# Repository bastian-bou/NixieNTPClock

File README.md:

# NixieNTPClock
Nixie clock around ESP32 connected to a NTP server

You can find the KiCad project and gerbers in **Hardware** folder and the PlatformIO project with arduino framwork in **Software** project

I am using ESP32 WROOM 32

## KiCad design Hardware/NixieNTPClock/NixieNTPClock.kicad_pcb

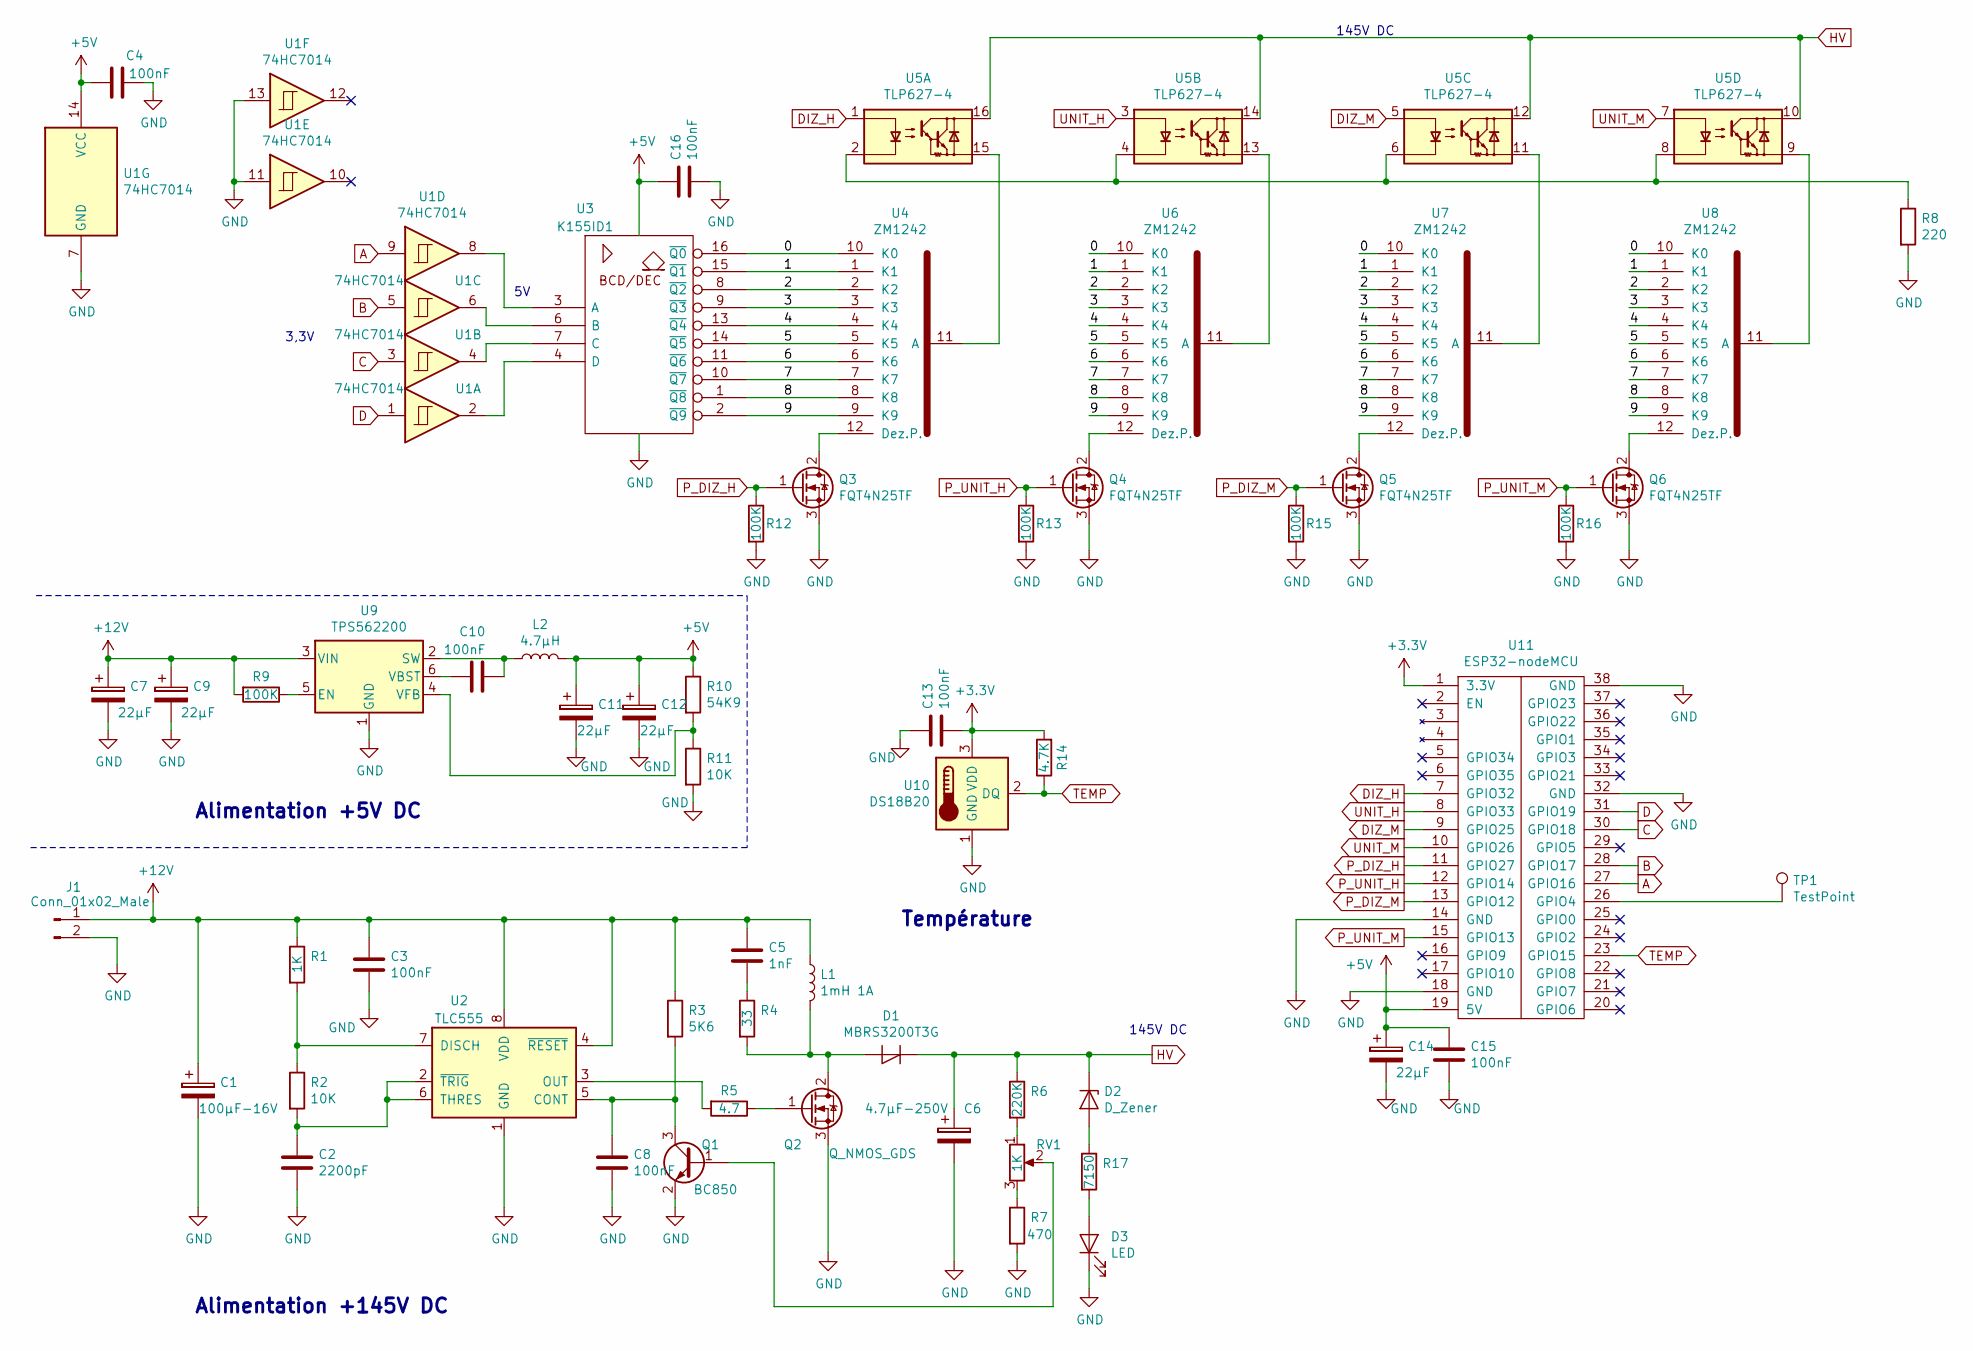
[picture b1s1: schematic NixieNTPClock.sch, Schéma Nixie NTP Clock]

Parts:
C1: 100µF-16V; CP_Elec_6.3x7.7; Farnell 1850114
C2: 2200pF; C_0603_HandSoldering; Farnell 2470451
C3, C4, C8, C10, C13, C15, C16: 100nF; C_0805_HandSoldering; Farnell 1740665
C5: 1nF; C_0603_HandSoldering
C6: 4.7µF-250V; CP_Elec_10x7.7; Farnell 2326350
C7, C9, C11, C12, C14: 22µF; CP_Elec_5x5.8; Farnell 9695737
D1: MBRS3200T3G; D_SMB_Handsoldering; Farnell 1838812
D2: D_Zener; D_SMB_Handsoldering; Farnell 2844801
D3: LED; D_0603; Farnell 8529833
J1: Conn_01x02_Male; PINHEAD1-2
L1: 1mH 1A; Inductor_Wurth_HCI-1335; Farnell 2288316
L2: 4.7µH; SELF-WE-TPC_M; Farnell 2066938
Q1: BC850; SOT-23W_Handsoldering; Farnell 1081241
Q2: Q_NMOS_GDS; TO-252-2; Farnell 2453852
Q3, Q4, Q5, Q6: FQT4N25TF; SOT-223-3_TabPin2; Farnell 2453914
R1: 1K; R_1206_HandSoldering
R2, R11: 10K; R_1206_HandSoldering
R3: 5K6; R_1206_HandSoldering
R4: 33; R_1206_HandSoldering
R5: 4.7; R_1206_HandSoldering
R6: 220K; R_1206_HandSoldering
R7: 470; R_1206_HandSoldering
R8: 220; R_1206_HandSoldering
R9, R12, R13, R15, R16: 100K; R_1206_HandSoldering
R10: 54K9; R_1206_HandSoldering
R14: 4.7K; R_1206_HandSoldering
R17: 7150; R_1206_HandSoldering; Farnell 2307836
RV1: 1K; Potentiometer_Trimmer_Vishay_TS53YJ; Farnell 1141482
TP1: TestPoint; touch
U1: 74HC7014; SOIC-14_3.9x8.7mm_Pitch1.27mm; Farnell 2777749
U2: TLC555; DIP-8_W7.62mm_SMDSocket_SmallPads
U3: K155ID1; DIP-16_W7.62mm_Socket
U4, U6, U7, U8: ZM1242
U5: TLP627-4; DIP-16_W7.62mm_Socket_LongPads; Farnell 1225840
U9: TPS562200; SOT-23-6; Farnell 2781737
U10: DS18B20; TO-92_Inline_Wide
U11: ESP32-nodeMCU; ESP32 NodeMCU AZ

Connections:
+3V3: C13.2, R14.2, U10.3 (VDD), U11.1 (3.3V)
+5V: C4.1, C11.1, C12.1, C14.1, C15.1, C16.1, L2.2, R10.1, U1.14 (VCC), U3.5 (VCC), U11.19 (5V)
+12V: C1.1, C3.1, C5.1, C7.1, C9.1, J1.1, L1.1, R1.1, R3.1, R9.2, U2.4 (~RESET), U2.8 (VDD), U9.3 (VIN)
/0: U3.16 (~Q0), U4.10 (K0), U6.10 (K0), U7.10 (K0), U8.10 (K0)
/1: U3.15 (~Q1), U4.1 (K1), U6.1 (K1), U7.1 (K1), U8.1 (K1)
/2: U3.8 (~Q2), U4.2 (K2), U6.2 (K2), U7.2 (K2), U8.2 (K2)
/3: U3.9 (~Q3), U4.3 (K3), U6.3 (K3), U7.3 (K3), U8.3 (K3)
/4: U3.13 (~Q4), U4.4 (K4), U6.4 (K4), U7.4 (K4), U8.4 (K4)
/5: U3.14 (~Q5), U4.5 (K5), U6.5 (K5), U7.5 (K5), U8.5 (K5)
/6: U3.11 (~Q6), U4.6 (K6), U6.6 (K6), U7.6 (K6), U8.6 (K6)
/7: U3.10 (~Q7), U4.7 (K7), U6.7 (K7), U7.7 (K7), U8.7 (K7)
/8: U3.1 (~Q8), U4.8 (K8), U6.8 (K8), U7.8 (K8), U8.8 (K8)
/9: U3.2 (~Q9), U4.9 (K9), U6.9 (K9), U7.9 (K9), U8.9 (K9)
A: U1.9, U11.27 (GPIO16)
B: U1.5, U11.28 (GPIO17)
C: U1.3, U11.30 (GPIO18)
D: U1.1, U11.31 (GPIO19)
DIZ_H: U5.1, U11.7 (GPIO32)
DIZ_M: U5.5, U11.9 (GPIO25)
GND: C1.2, C2.2, C3.2, C4.2, C6.2, C7.2, C8.2, C9.2, C11.2, C12.2, C13.1, C14.2, C15.2, C16.2, D3.1 (K), J1.2, Q1.2 (E), Q2.3 (S), Q3.3 (S), Q4.3 (S), Q5.3 (S), Q6.3 (S), R7.2, R8.2, R11.2, R12.2, R13.2, R15.2, R16.2, U1.7 (GND), U1.11, U1.13, U2.1 (GND), U3.12 (GND), U9.1 (GND), U10.1 (GND), U11.14 (GND), U11.18 (GND), U11.32 (GND), U11.38 (GND)
HV: C6.1, D1.1 (K), D2.1 (K), R6.1, U5.10, U5.12, U5.14, U5.16
unnamed: C2.1, R2.2, U2.2 (~TRIG), U2.6 (THRES)
unnamed: C5.2, R4.1
unnamed: C8.1, Q1.3 (C), R3.2, U2.5 (CONT)
unnamed: C10.1, U9.6 (VBST)
unnamed: C10.2, L2.1, U9.2 (SW)
unnamed: D1.2 (A), L1.2, Q2.2 (D), R4.2
unnamed: D2.2 (A), R17.1
unnamed: D3.2 (A), R17.2
unnamed: Q1.1 (B), RV1.2
unnamed: Q2.1 (G), R5.1
unnamed: Q3.2 (D), U4.12 (Dez.P.)
unnamed: Q4.2 (D), U6.12 (Dez.P.)
unnamed: Q5.2 (D), U7.12 (Dez.P.)
unnamed: Q6.2 (D), U8.12 (Dez.P.)
unnamed: R1.2, R2.1, U2.7 (DISCH)
unnamed: R5.2, U2.3 (OUT)
unnamed: R6.2, RV1.1
unnamed: R7.1, RV1.3
unnamed: R8.1, U5.2, U5.4, U5.6, U5.8
unnamed: R9.1, U9.5 (EN)
unnamed: R10.2, R11.1, U9.4 (VFB)
unnamed: TP1.1, U11.26 (GPIO4)
unnamed: U1.2, U3.4 (D)
unnamed: U1.4, U3.7 (C)
unnamed: U1.6, U3.6 (B)
unnamed: U1.8, U3.3 (A)
unnamed: U4.11 (A), U5.15
unnamed: U5.9, U8.11 (A)
unnamed: U5.11, U7.11 (A)
unnamed: U5.13, U6.11 (A)
P_DIZ_H: Q3.1 (G), R12.1, U11.11 (GPIO27)
P_DIZ_M: Q5.1 (G), R15.1, U11.13 (GPIO12)
P_UNIT_H: Q4.1 (G), R13.1, U11.12 (GPIO14)
P_UNIT_M: Q6.1 (G), R16.1, U11.15 (GPIO13)
TEMP: R14.1, U10.2 (DQ), U11.23 (GPIO15)
UNIT_H: U5.3, U11.8 (GPIO33)
UNIT_M: U5.7, U11.10 (GPIO26)

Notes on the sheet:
145V DC
3,3V
Alimentation +5V DC
Alimentation +145V DC
Température

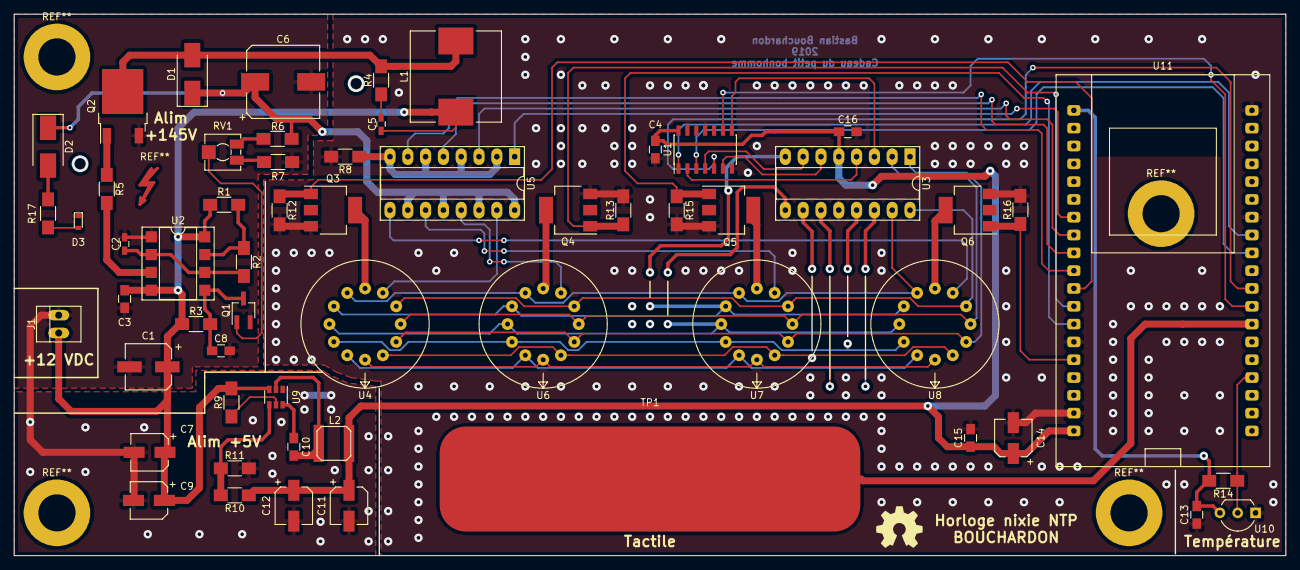
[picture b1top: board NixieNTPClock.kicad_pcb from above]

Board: 4 copper layers, 181.4 x 77.2 mm, 58 parts (0 on the bottom side), 58 nets.

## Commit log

2019-10-21 Update README.md
    Add comments on library and folders description
2019-10-22 add Hardware and Software folders
2019-10-27 Add kicad project files with a beginning of schematic (high voltage power supply unit)
2019-10-27 Add documentation with siemens datasheet Add farnel refs and component refs in schematic
2019-10-27 Add nixie command in schema, nixie library in project and pdf in documentation
2019-10-28 remove DOC folder
2019-10-28 nixie command finished, add 5V DC power supply and temp sensor
2019-10-28 Add command code for farnell in schematic
2019-10-29 Add ESP32 NODE MCU library + labels for connection with ESP32
2019-10-30 add software project from platformio
2019-10-30 Add NixieClock library + methods Add getTemp() + isTouch() functions beginning of loop()
2019-10-30 Add multiple references (not finished) Finish schematic
2019-10-30 add no important things
2019-11-02 Update Schema Add footprint library Finish netlist Started rooting
2019-11-04 add state machine and debug macro
2019-11-08 Continu on PCB ...
2019-11-12 Hardware: power supply
2019-11-15 debug nixie lib + TODO: fix debug.print
2019-11-20 Continuous routing ...
2019-11-24 PCB almost finished
2019-11-25 Finished PCB and added pdf and gerber files
2019-11-25 Add gerber files, zip and PDF
2019-11-27 add some stuff wifi manager, finished nixie
2019-11-27 Add BOM list
2019-11-28 Add simple wifi connexion, add new methods in Nixie lib with animation, temperature, clear ...
2019-12-09 Wifi is working, all the features are working except Temp because I don't have the sensor yet
2019-12-17 Improve the method to display temp ant time Add parameter to set tubes with specific values in refresh Imporve NTP get time after temperature
2019-12-18 Add comments on methods in nixie library and modify a little bit the setup (move nixieOn)
2019-12-22 Modify the state machine, remove waiting state to have the same on duration for all digits. Put le refresh frequency at 60H
2019-12-23 Add test loop if you touch capacitive button at start Add testNixie method in Nixie library Add datasheet of TLP627 opto-darlington
2019-12-24 fix decimal temperature and add NOP() in refresh nixie tubes
2020-01-11 Update every hour with NTP server Fix Time shifting
2020-03-11 Resolve rollover on µs timeout Add macro to cast esp_timer_get_time() into unsigned 64 bits
2023-12-24 Remove old lib + change NTP to add daylight saving time, ...
2023-12-24 Add comments, improve code, add preprocessor error with info about params.h
